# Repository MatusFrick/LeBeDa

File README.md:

# LeBeDa
GERBER and kicad files are in [lbd](lbd) folder

Sloth on silkscreen from:
[Sloth icons created by Vitaly Gorbachev - Flaticon](https://www.flaticon.com/free-icons/sloth)

Parts:
- PCB
- 34 kailh hotswap  sockets 
- 34 kailh switchs and keycaps
- battery 3.7V 100mAh
- 2 power buttons (get more if you do not know how to solder :D )
- 2x nice!nano V2
- sockets and pins for nano
- JST connector for battery

Assembly:
- Solder hotswap sockets
- Solder pins to nice!nano | left one is upside down !
- Solder battery connector and nice nano sockets
- Put everything together
- Flash nice!nano with ZMK software - [My colemak config](https://github.com/MatusFrick/zmk-config)

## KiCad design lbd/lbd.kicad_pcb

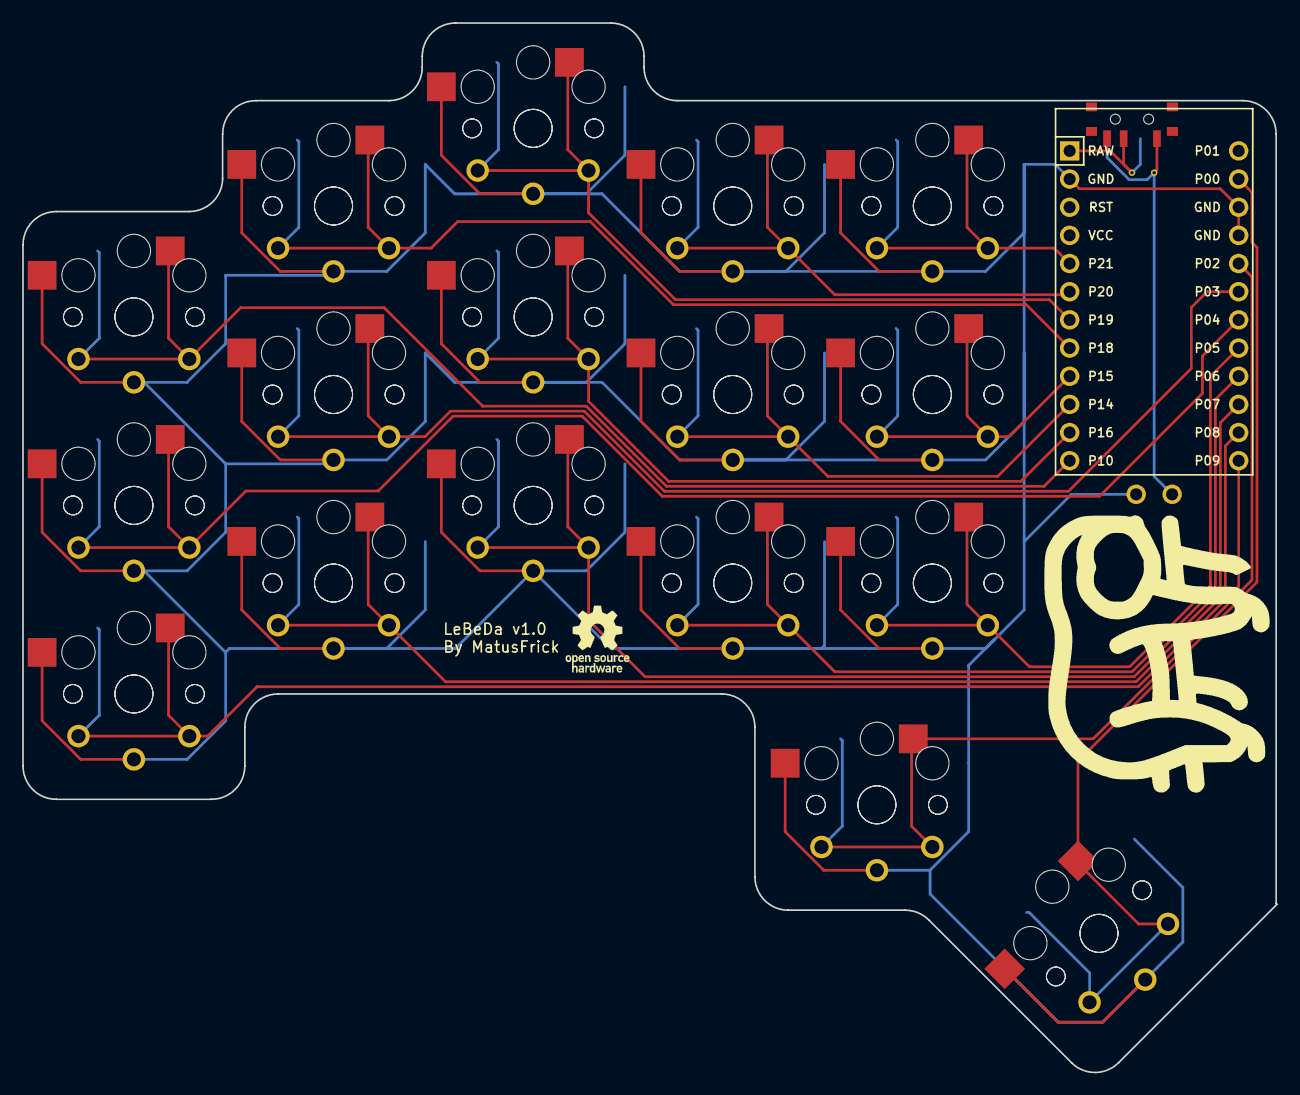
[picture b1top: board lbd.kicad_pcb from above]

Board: 2 copper layers, 113.1 x 94.6 mm, 35 parts (0 on the bottom side), 18 nets.

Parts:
MCU1: ProMicro
S1, S2, S3, S4, S5, S6, S7, S8, S9, S10, S11, S12, S13, S14, S15, S16, S17, S18, S19, S20, S21, S22, S23, S24, S25, S26, S27, S28, S29, S30, S31, S32, S33, S34: PG1350

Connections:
GND: MCU1.2, MCU1.15, MCU1.16, S1.2, S2.2, S3.2, S4.2, S5.2, S6.2, S7.2, S8.2, S9.2, S10.2, S11.2, S12.2, S13.2, S14.2, S15.2, S16.2, S17.2, S18.2, S19.2, S20.2, S21.2, S22.2, S23.2, S24.2, S25.2, S26.2, S27.2, S28.2, S29.2, S30.2, S31.2, S32.2, S33.2, S34.2
P0: MCU1.14, S33.1, S34.1
P2: MCU1.17, S31.1, S32.1
P3: MCU1.18, S9.1, S10.1
P4: MCU1.19, S3.1, S4.1
P5: MCU1.20, S25.1, S26.1
P6: MCU1.21, S19.1, S20.1
P7: MCU1.22, S13.1, S14.1
P8: MCU1.23, S7.1, S8.1
P9: MCU1.24, S1.1, S2.1
P10: MCU1.12, S5.1, S6.1
P14: MCU1.10, S21.1, S22.1
P15: MCU1.9, S27.1, S28.1
P16: MCU1.11, S15.1, S16.1
P18: MCU1.8, S11.1, S12.1
P19: MCU1.7, S17.1, S18.1
P20: MCU1.6, S23.1, S24.1
P21: MCU1.5, S29.1, S30.1

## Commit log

2022-04-03 Routed with silk screen
2022-04-03 Add 3D render to readme
2022-04-03 Add Gerber files
2022-11-11 Add parts and assembly
